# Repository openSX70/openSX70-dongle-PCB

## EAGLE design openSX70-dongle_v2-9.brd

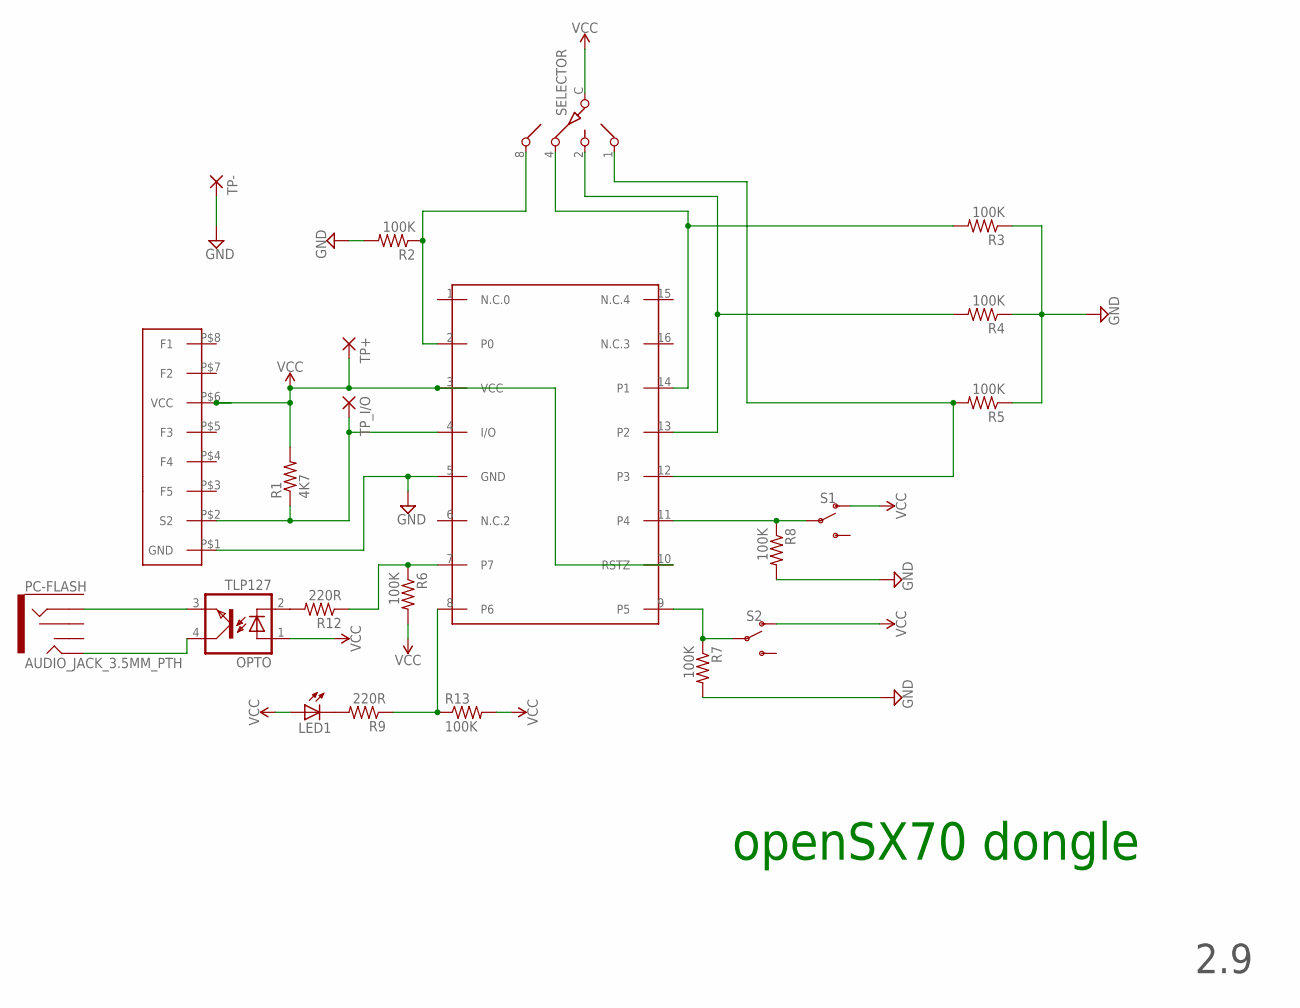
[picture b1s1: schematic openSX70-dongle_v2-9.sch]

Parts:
DS2408: DS2408; SO16
LED1: LED3MM
OPTO: TLP127; SO-4
PC-FLASH: AUDIO_JACK_3.5MM_PTH; AUDIO-JACK
R1: 4K7; M0805
R2, R3, R4, R5, R6, R7, R8, R13: 100K; M0805
R9, R12: 220R; M0805
S1, S2: SWITCH-SPDT-SMD-RIGHT-ANGLE; SWITCH_SPST_SMD_A
SELECTOR: SW-C16
TP+: SMD2; SMD1,27-2,54
TP-: SMD2; SMD1,27-2,54
TP_I/O: SMD2; SMD1,27-2,54
U$1: FLASH-EDGE-CONNECTOR; FLASH-EDGE-8

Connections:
GND: DS2408.5 (GND), R2.2, R3.1, R4.1, R5.1, R7.2, R8.2, TP-.1, U$1.P$1 (GND)
unnamed: DS2408.4 (I/O), R1.1, TP_I/O.1, U$1.P$2 (S2)
unnamed: LED1.K (C), R9.2
unnamed: DS2408.2 (P0), R2.1, SELECTOR.8
unnamed: DS2408.14 (P1), R3.2, SELECTOR.4
unnamed: DS2408.13 (P2), R4.2, SELECTOR.2
unnamed: DS2408.11 (P4), R8.1, S1.2
unnamed: DS2408.9 (P5), R7.1, S2.2
unnamed: DS2408.8 (P6), R9.1, R13.1
unnamed: OPTO.2 (C), R12.2
unnamed: DS2408.7, R6.1, R12.1
unnamed: OPTO.4 (COL), PC-FLASH.TIP
unnamed: DS2408.12 (P3), R5.2, SELECTOR.1
unnamed: OPTO.3 (EMIT), PC-FLASH.RING
VCC: DS2408.3 (VCC), DS2408.10 (RSTZ), LED1.A, OPTO.1 (A), R1.2, R6.2, R13.2, S1.1 (O), S2.1 (O), SELECTOR.C, TP+.1, U$1.P$6 (VCC)

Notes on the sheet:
openSX70 dongle
2.9

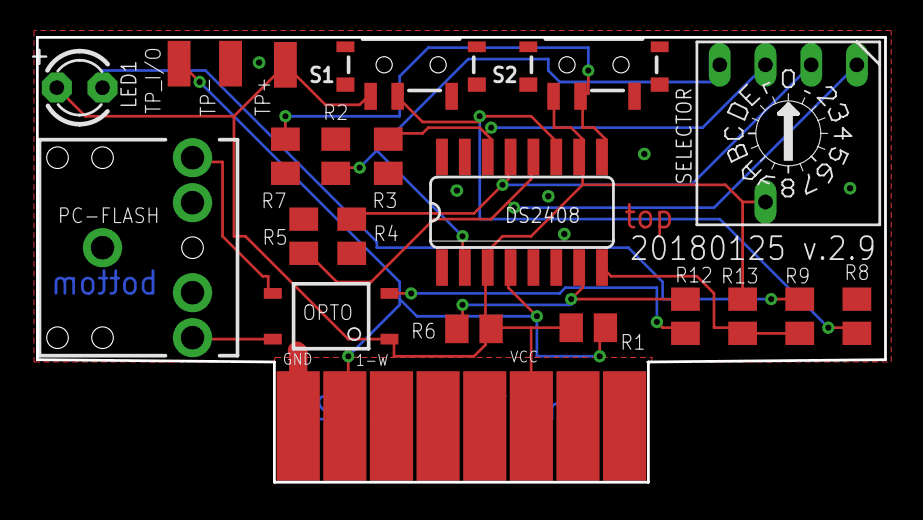
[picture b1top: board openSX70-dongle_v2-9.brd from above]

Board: 2 copper layers, 47.1 x 24.7 mm, 22 parts (0 on the bottom side), 15 nets.

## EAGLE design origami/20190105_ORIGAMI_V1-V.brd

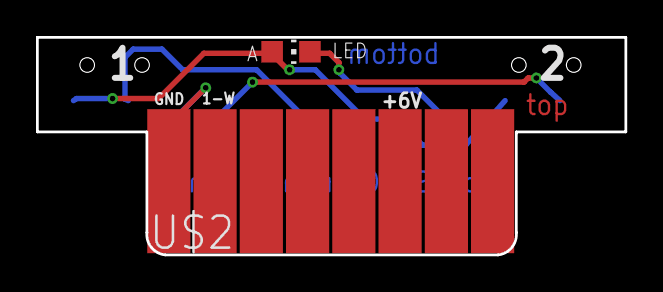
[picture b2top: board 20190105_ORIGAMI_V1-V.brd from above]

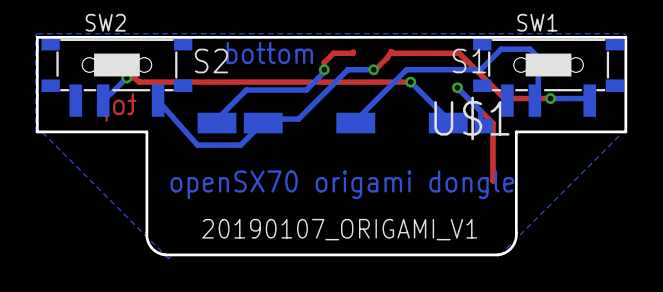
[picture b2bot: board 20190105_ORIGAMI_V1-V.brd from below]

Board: 2 copper layers, 32.7 x 12.1 mm, 5 parts (3 on the bottom side), 5 nets.

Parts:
LED: CHIP-LED0805
SW1, SW2: MK-12C02 G1.5; SW7-SMD-L6.7X2.7X3.2MM
U$1: FLASH-BRIDGE-SW1-SW2-LED-SMALL; FLASH-8-BRIDGE-SW1-SW2-LED-SMALL
U$2: SX70-FLASH-EDGE8-MALE-LONG; SX70-FLASH-EDGE8-2

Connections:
2.8V-V: LED.A, SW1.A, SW2.A, U$1.VCC-2.8V
unnamed: U$1.GND, U$2.GND
unnamed: SW1.COM, U$1.SWITCH-1
unnamed: SW2.COM, U$1.SWITCH-2
unnamed: LED.C, U$1.LED

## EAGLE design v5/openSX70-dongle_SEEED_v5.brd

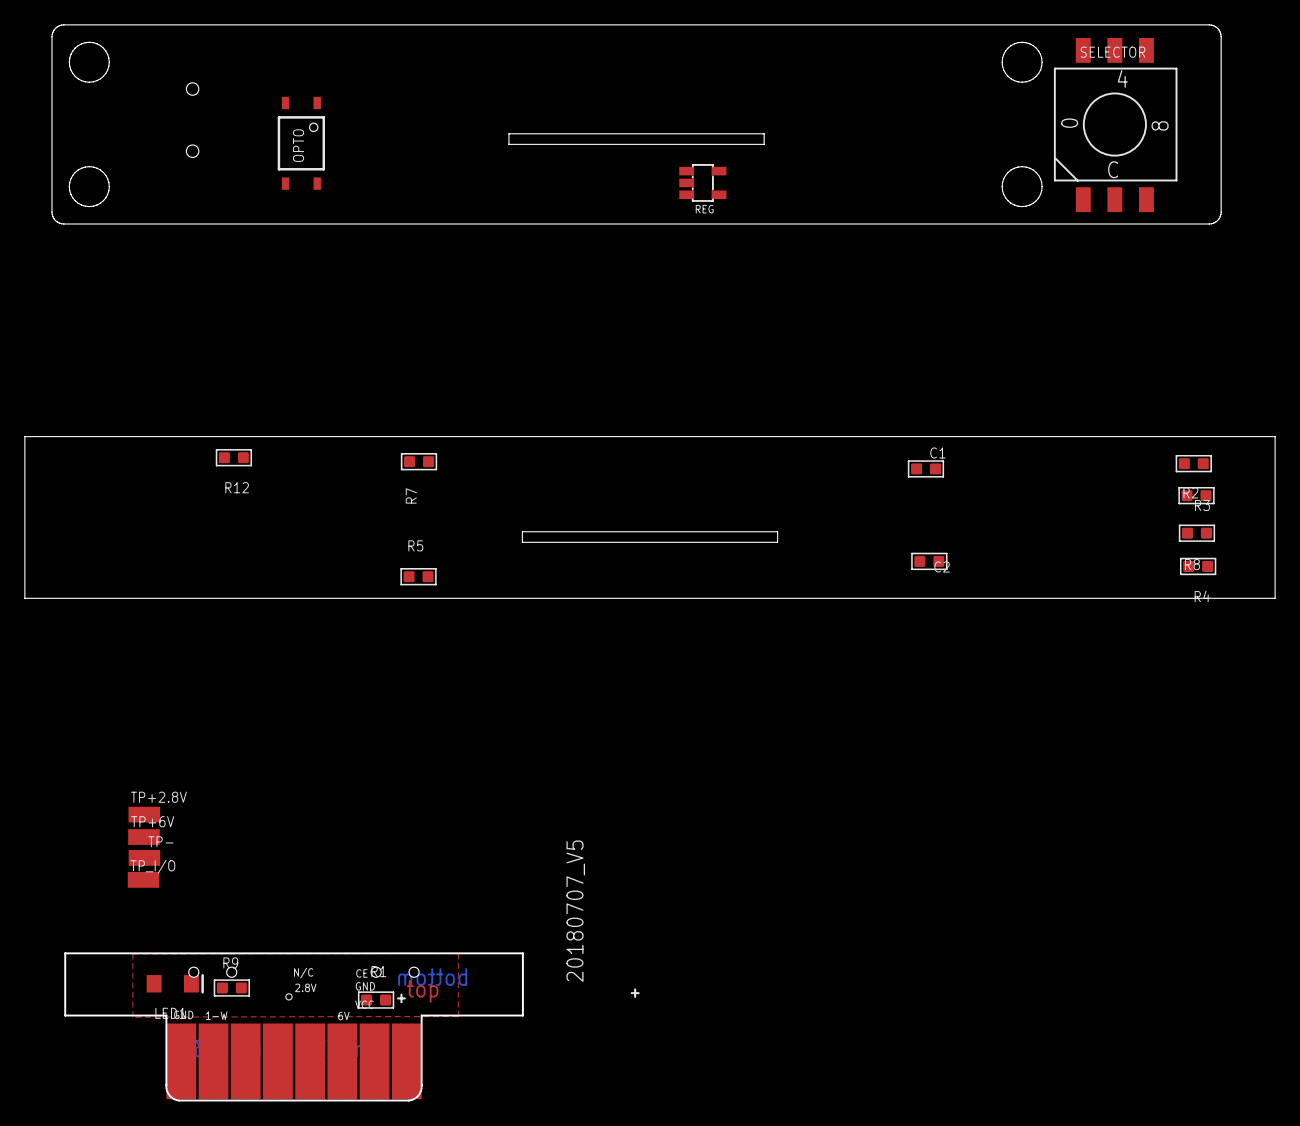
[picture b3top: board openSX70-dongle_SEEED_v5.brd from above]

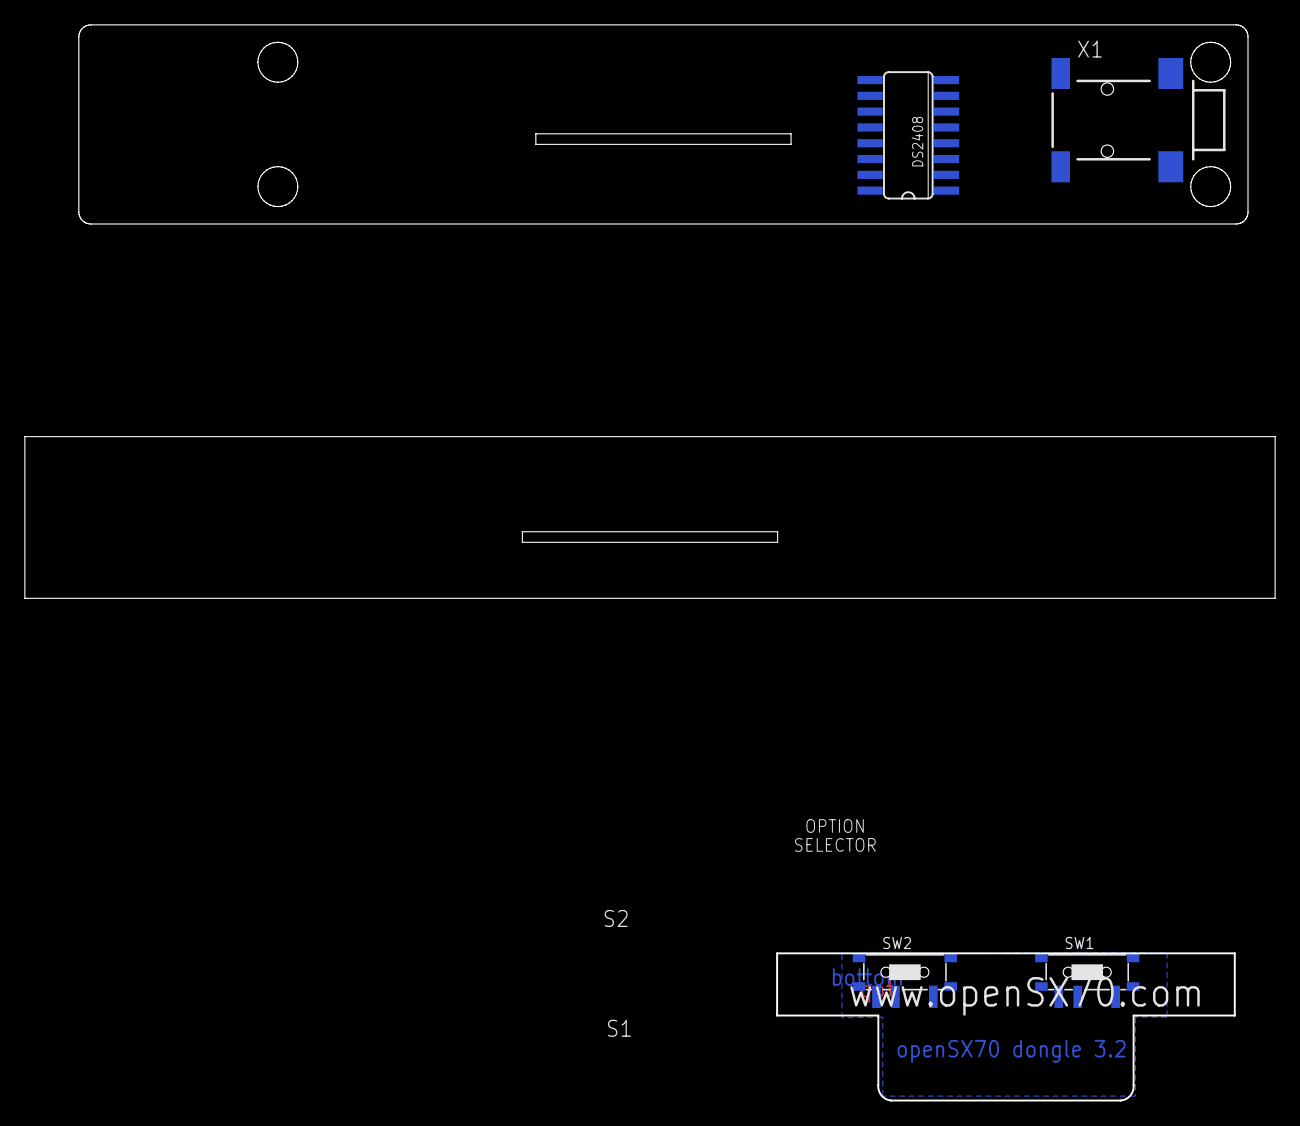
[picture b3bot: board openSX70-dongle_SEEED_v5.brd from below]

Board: 2 copper layers, 100.5 x 86.5 mm, 24 parts (4 on the bottom side), 16 nets, no tracks yet.

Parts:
C1, C2: 1uf; C0603
DS2408: DS2408; SO16
LED1: Yellow; LED-1206
OPTO: TLP127; SO-4
R1: 4.7K; R0603
R2, R3, R4, R5, R7, R8: 100K; R0603
R9, R12: 220R; R0603
REG: NCP4688; SOT-23-5
SELECTOR: CTS221AMX16
SW1, SW2: MK-12C02 G1.5; SW7-SMD-L6.7X2.7X3.2MM
TP+2.8V, TP+6V: SMD1,27-2,54
TP-: SMD1,27-2,54
TP_I/O: SMD1,27-2,54
U$1: FLASH-EDGE-CONNECTOR; FLASH-EDGE-8
X1: 1503_02

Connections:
2.8V: C2.1, DS2408.3, DS2408.10, LED1.A, OPTO.1, R1.2, REG.5, SELECTOR.C, SELECTOR.C2, SW1.A, SW2.A, TP+2.8V.1
GND: C1.2, C2.2, DS2408.5, R2.2, R3.1, R4.1, R5.1, R7.2, R8.2, REG.2, TP-.1, U$1.P$1
unnamed: DS2408.4, R1.1, TP_I/O.1, U$1.P$2
unnamed: LED1.C, R9.2
unnamed: DS2408.2, R2.1, SELECTOR.8
unnamed: DS2408.14, R3.2, SELECTOR.4
unnamed: DS2408.13, R4.2, SELECTOR.2
unnamed: DS2408.11, R8.1, SW2.COM
unnamed: DS2408.9, R7.1, SW1.COM
unnamed: DS2408.8, R9.1
unnamed: OPTO.4, X1.2, X1.3
unnamed: OPTO.2, R12.2
unnamed: DS2408.7, R12.1
unnamed: DS2408.12, R5.2, SELECTOR.1
unnamed: OPTO.3, X1.1
VCC: C1.1, REG.1, REG.3, TP+6V.1, U$1.P$6

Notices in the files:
parts and their libraries:
SparkFun-Connectors: Licensing: Creative Commons ShareAlike 4.0 International - https://creativecommons.org/licenses/by-sa/4.0
